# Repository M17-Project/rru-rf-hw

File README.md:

[![CC BY-NC-SA 4.0][cc-by-nc-sa-shield]][cc-by-nc-sa]

# rru-rf-hw
Remote Radio Unit RF board.

## What is it?
An FM repeater in a milled aluminum chassis. Built around a pair of [CC1200 chips](https://www.ti.com/product/CC1200) from Texas Instruments and an RF power amplifier module.
Revision A with CC1200 RF front-ends supports various FM-based modes, including M17 and AFSK.

## Quick fact sheet
RF power module - [RA60H3847M1](https://www.mitsubishielectric.com/semiconductors/hf/products/datasheet/ra60h3847m1.pdf)<br>
RF output power - 1..60W continuous, up to 80W with lower duty cycle<br>
Frequency range - 420..450MHz<br>
Frequency error - <0.5 ppm over -40 to +85°C range<br>
Supply voltage - 13.8V DC<br>
Power consumption - <150W at 60W RF out<br>
Load mismatch immunity - continuous over the whole VSWR range (built in RF isolator)<br>
Harmonic content - 2nd <-40dBc, 3rd <-55dBc (435MHz at 48.3dBm)<br>
Mode support: analog FM, M17, (A)FSK<br>
Circulator:  WH3538X-1, 400..470MHz (microstrip)<br>
Dummy load: Anaren [J100N50X4B](https://www.mouser.pl/datasheet/2/21/J100N50X4B-3364610.pdf)<br>

## Firmware
A basic, "crash-test" frmware template is available [here](https://github.com/M17-Project/rru-rf-fw).

### Flashing the MCU over UART
- Build the firmware using CubeIDE
- Copy the .bin file over to Raspberry Pi
- Run `stm32flash -v -R -i "-539&-529&539,529,:-539,-529,529" -w rru-rf-fw.bin /dev/ttyAMA0`

In case of problems, see [this](https://github.com/M17-Project/rpi-interface?tab=readme-ov-file#flashing-the-target-device-cc1200-hat) for some additional explanation.

## Chassis
Milled aluminum chassis is required. A reference design can be obtained from a [separate repository](https://github.com/M17-Project/rru-rf-chassis).

## Revision history
### Revision A
Initial revision.

### Revision B
* Switched mode voltage regulators have been replaced with linear.
* Added a buffer between the 40 MHz reference TCXO and transceiver ICs.
* Added bleeder resistors at the RF PA and 13.8V power supply.
* Slightly improved ALC circuit.
* Reduced N-connector cutouts (4.5mm down to 2mm).
* Added decoupling capacitor arrays at both RF PA's supply and VGG pins.
* DA15 connector now has MCU's BOOT0 signal available at pin 13.
* Bodge wire mod is no longer required, as both baseband trigger signals are now routed to the MCU.

### Revision C
* Added a lowpass filter after the RF PA stage
* Added a bandpass filter at the RF input
* TX and RX blocks are now clocked independently
* Pull-down resistor at TP2 (BOOT1)

## License
This work is licensed under a
[Creative Commons Attribution-NonCommercial-ShareAlike 4.0 International License][cc-by-nc-sa].

[![CC BY-NC-SA 4.0][cc-by-nc-sa-image]][cc-by-nc-sa]

[cc-by-nc-sa]: http://creativecommons.org/licenses/by-nc-sa/4.0/
[cc-by-nc-sa-image]: https://licensebuttons.net/l/by-nc-sa/4.0/88x31.png
[cc-by-nc-sa-shield]: https://img.shields.io/badge/License-CC%20BY--NC--SA%204.0-lightgrey.svg

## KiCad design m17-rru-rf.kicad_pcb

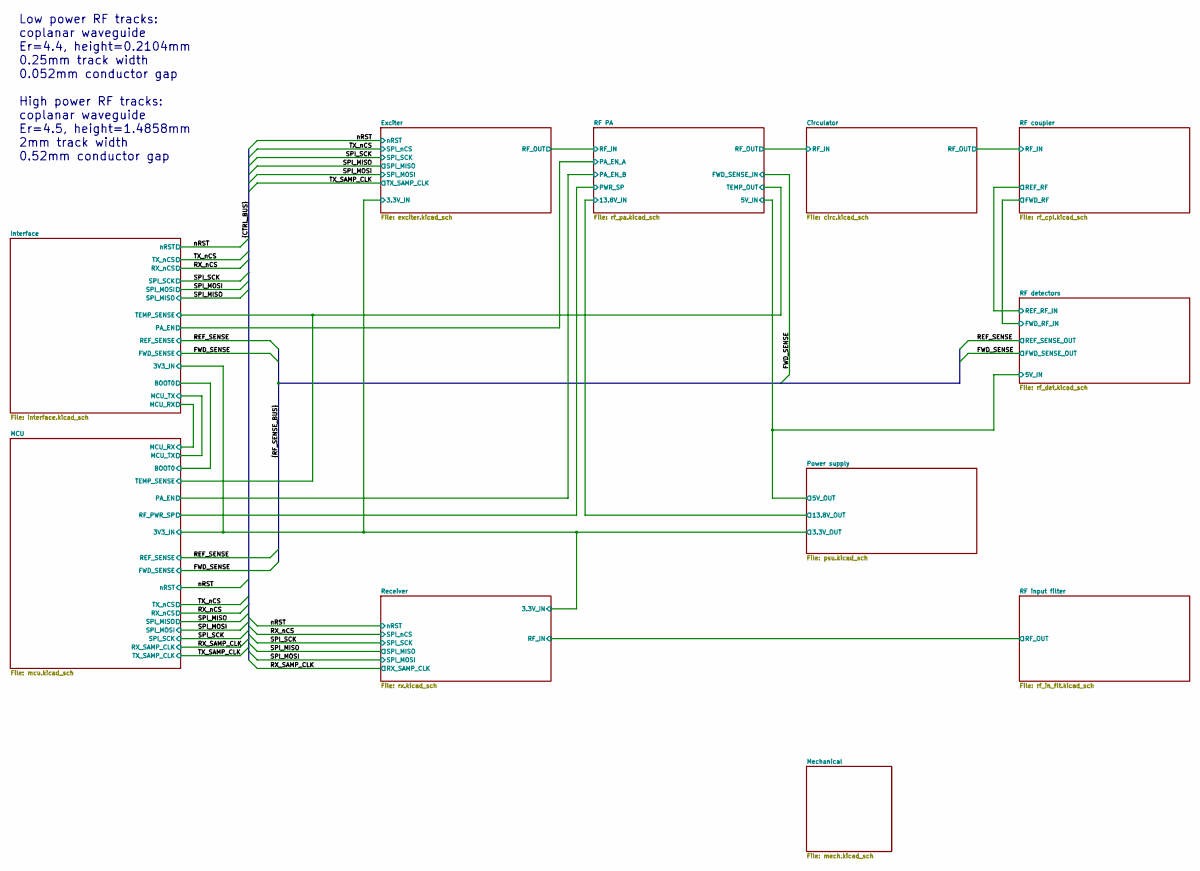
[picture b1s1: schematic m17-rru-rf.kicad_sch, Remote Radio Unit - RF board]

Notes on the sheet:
Low power RF tracks: coplanar waveguide Er=4.4, height=0.2104mm 0.25mm track width 0.052mm conductor gap High power RF tracks: coplanar waveguide Er=4.5, height=1.4858mm 2mm track width 0.52mm conductor gap

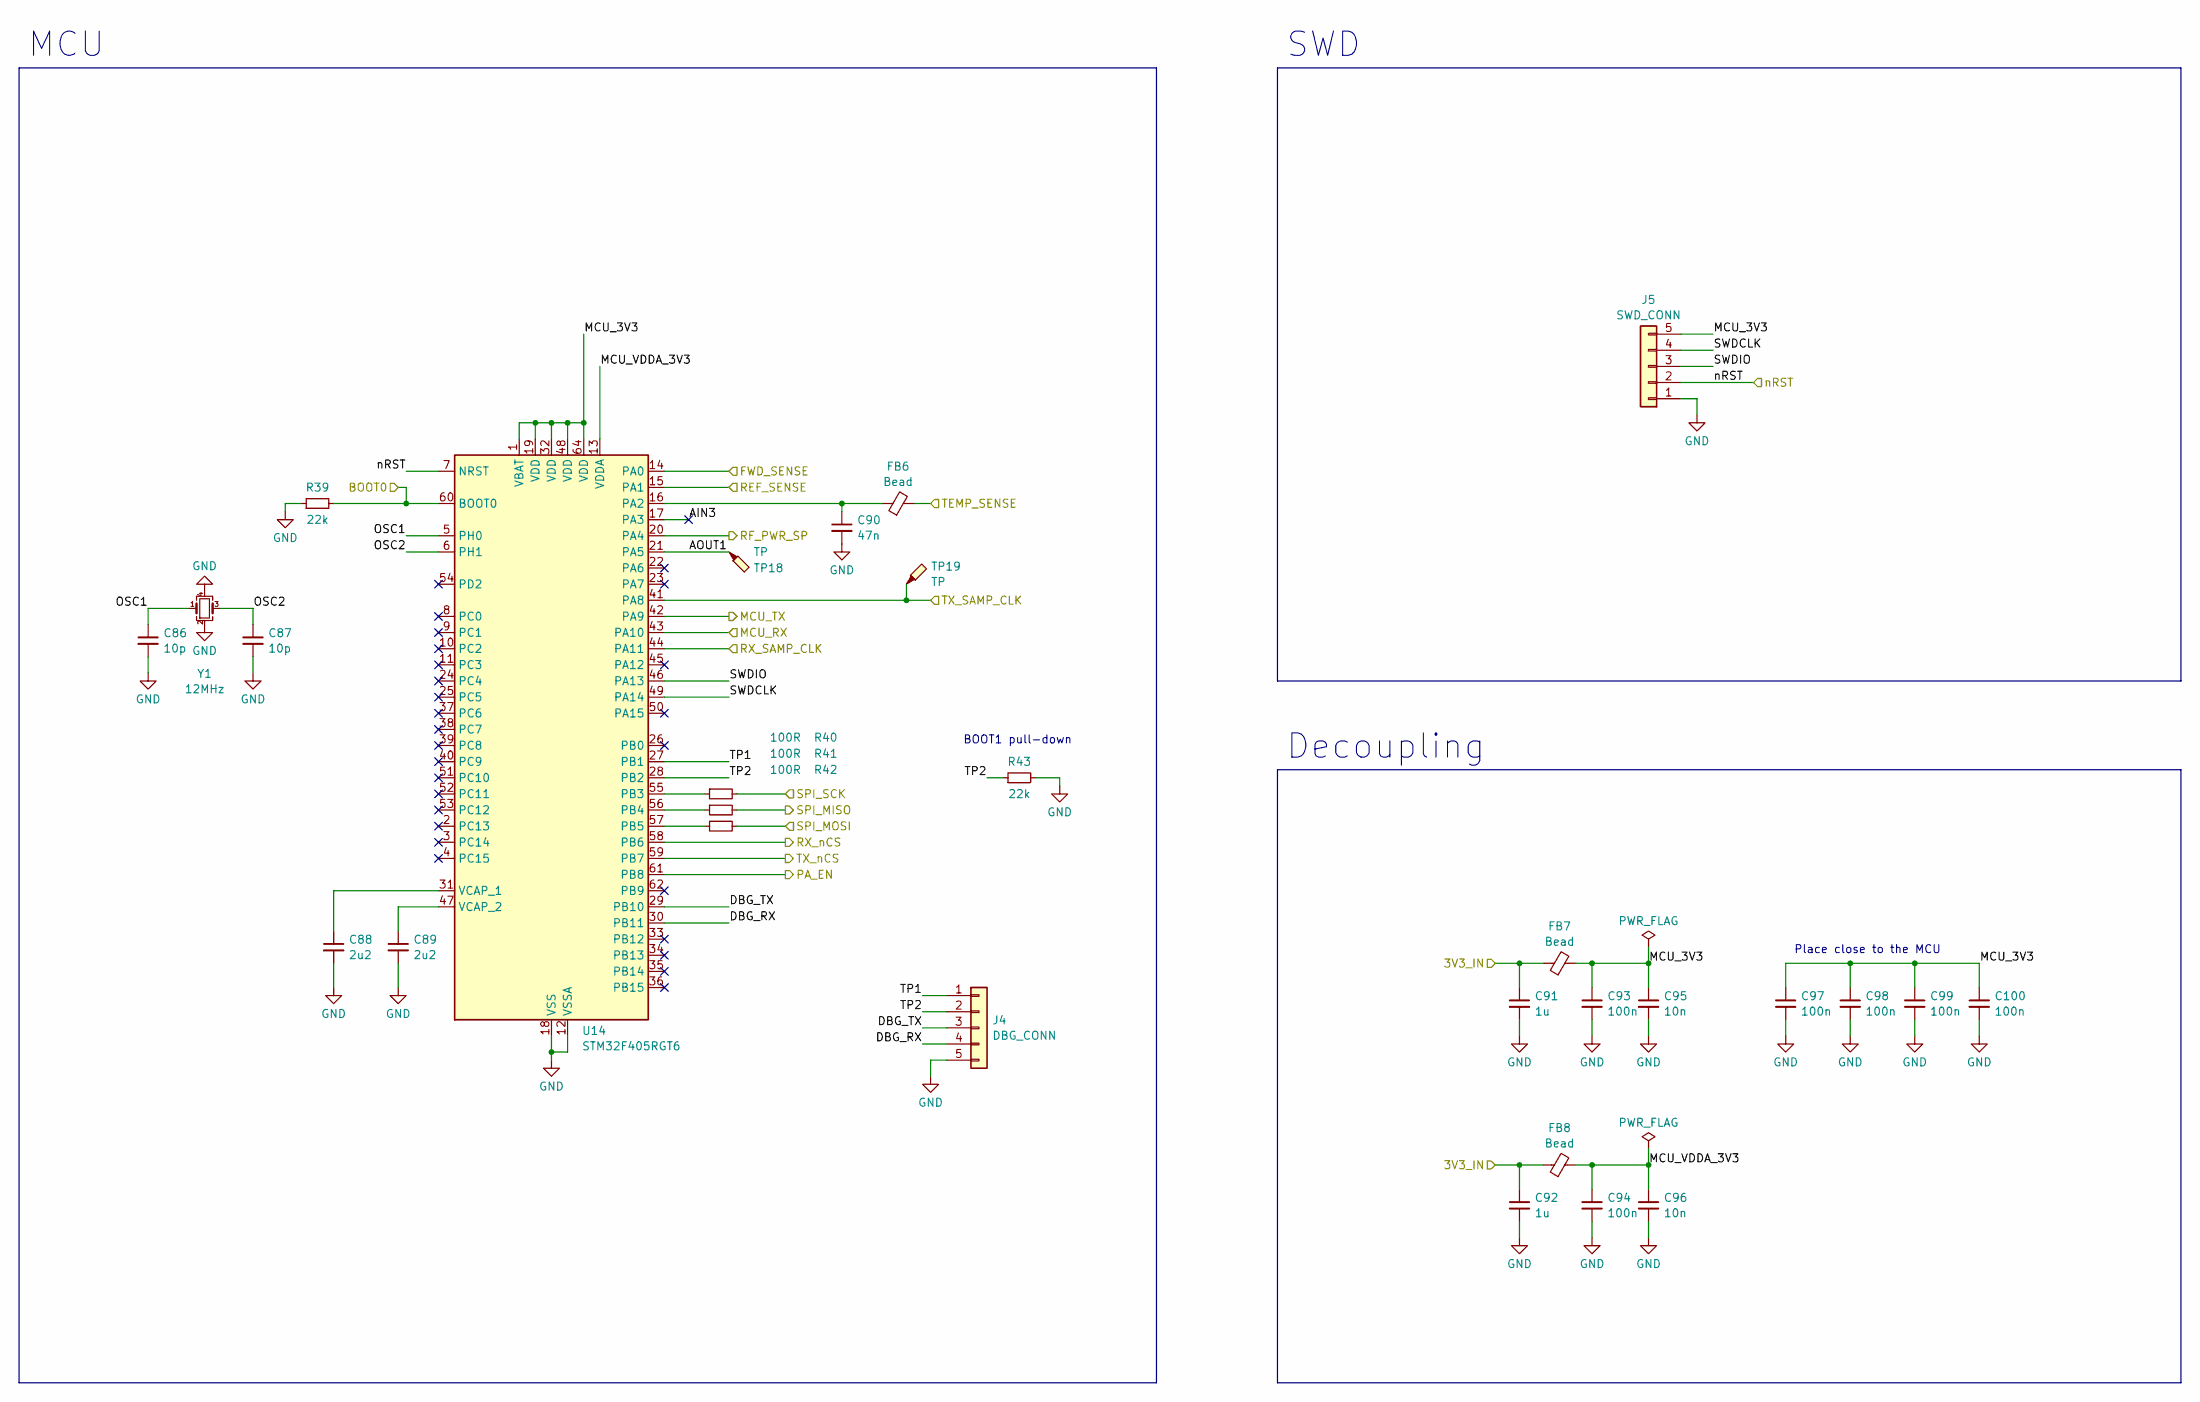
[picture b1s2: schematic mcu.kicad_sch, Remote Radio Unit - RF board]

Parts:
C86, C87: 10p; C_0603_1608Metric; MPN 06035A100JAT2A
C88, C89: 2u2; C_0603_1608Metric; MPN GRM188R61H225ME11J
C90: 47n; C_0603_1608Metric; MPN C0603C473K5RACTU
C91, C92: 1u; C_0603_1608Metric; MPN CL10B105KB8NQNC
C93, C94, C97, C98, C99, C100: 100n; C_0603_1608Metric; MPN C0603C104M5RAC7411
C95, C96: 10n; C_0603_1608Metric; MPN C0603C103K5RAC7081
FB6, FB7, FB8: Bead; L_0603_1608Metric; MPN BLM18KG601SH1D
J4: DBG_CONN; PinHeader_1x05_P2.54mm_Vertical_SMD_Pin1Left; MPN TSM-105-01-T-SV-TR
J5: SWD_CONN; PinHeader_1x05_P2.54mm_Vertical_SMD_Pin1Left; MPN TSM-105-01-T-SV-TR
R39, R43: 22k; R_0603_1608Metric; MPN CRGCQ0603J22K
R40, R41, R42: 100R; R_0603_1608Metric; MPN CRCW0603100RFKECC
TP18, TP19: TP; TestPoint_Pad_D1.5mm
U14: STM32F405RGT6; LQFP-64_10x10mm_P0.5mm; MPN STM32F405RGT6
Y1: 12MHz; Crystal_SMD_3225-4Pin_3.2x2.5mm; MPN ECS-120-12-33-AEN-TR

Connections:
/Exciter/3.3V_IN: C91.1, C92.1, FB7.1, FB8.1; also elsewhere on the board
/FWD_SENSE: U14.14 (PA0); also elsewhere on the board
/Interface/BOOT0: R39.2, U14.60 (BOOT0); also elsewhere on the board
/Interface/MCU_RX: U14.43 (PA10); also elsewhere on the board
/Interface/MCU_TX: U14.42 (PA9); also elsewhere on the board
/Interface/TEMP_SENSE: FB6.2; also elsewhere on the board
/MCU/AIN3: U14.17 (PA3)
/MCU/AOUT1: TP18.1, U14.21 (PA5)
/MCU/DBG_RX: J4.4, U14.30 (PB11)
/MCU/DBG_TX: J4.3, U14.29 (PB10)
/MCU/MCU_3V3: C93.1, C95.1, C97.1, C98.1, C99.1, C100.1, FB7.2, J5.5, U14.1 (VBAT), U14.19 (VDD), U14.32 (VDD), U14.48 (VDD), U14.64 (VDD)
/MCU/MCU_VDDA_3V3: C94.1, C96.1, FB8.2, U14.13 (VDDA)
/MCU/OSC1: C86.1, U14.5 (PH0), Y1.1
/MCU/OSC2: C87.1, U14.6 (PH1), Y1.3
/MCU/PA_EN: U14.61 (PB8); also elsewhere on the board
/MCU/RF_PWR_SP: U14.20 (PA4); also elsewhere on the board
/MCU/SWDCLK: J5.4, U14.49 (PA14)
/MCU/SWDIO: J5.3, U14.46 (PA13)
/MCU/TP1: J4.1, U14.27 (PB1)
/MCU/TP2: J4.2, R43.1, U14.28 (PB2)
/REF_SENSE: U14.15 (PA1); also elsewhere on the board
/RX_SAMP_CLK: U14.44 (PA11); also elsewhere on the board
/RX_nCS: U14.58 (PB6); also elsewhere on the board
/SPI_MISO: R41.2; also elsewhere on the board
/SPI_MOSI: R42.2; also elsewhere on the board
/SPI_SCK: R40.2; also elsewhere on the board
/TX_SAMP_CLK: TP19.1, U14.41 (PA8); also elsewhere on the board
/TX_nCS: U14.59 (PB7); also elsewhere on the board
/nRST: J5.2, U14.7 (NRST); also elsewhere on the board
GND: C86.2, C87.2, C88.2, C89.2, C90.2, C91.2, C92.2, C93.2, C94.2, C95.2, C96.2, C97.2, C98.2, C99.2, C100.2, J4.5, J5.1, R39.1, R43.2, U14.12 (VSSA), U14.18 (VSS), U14.63 (VSS), Y1.2, Y1.4; also elsewhere on the board
unnamed: C90.1, FB6.1, U14.16 (PA2)
unnamed: R40.1, U14.55 (PB3)
unnamed: R41.1, U14.56 (PB4)
unnamed: R42.1, U14.57 (PB5)
unnamed: C88.1, U14.31 (VCAP_1)
unnamed: C89.1, U14.47 (VCAP_2)

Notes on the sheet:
MCU
Place close to the MCU
BOOT1 pull-down
SWD
Decoupling

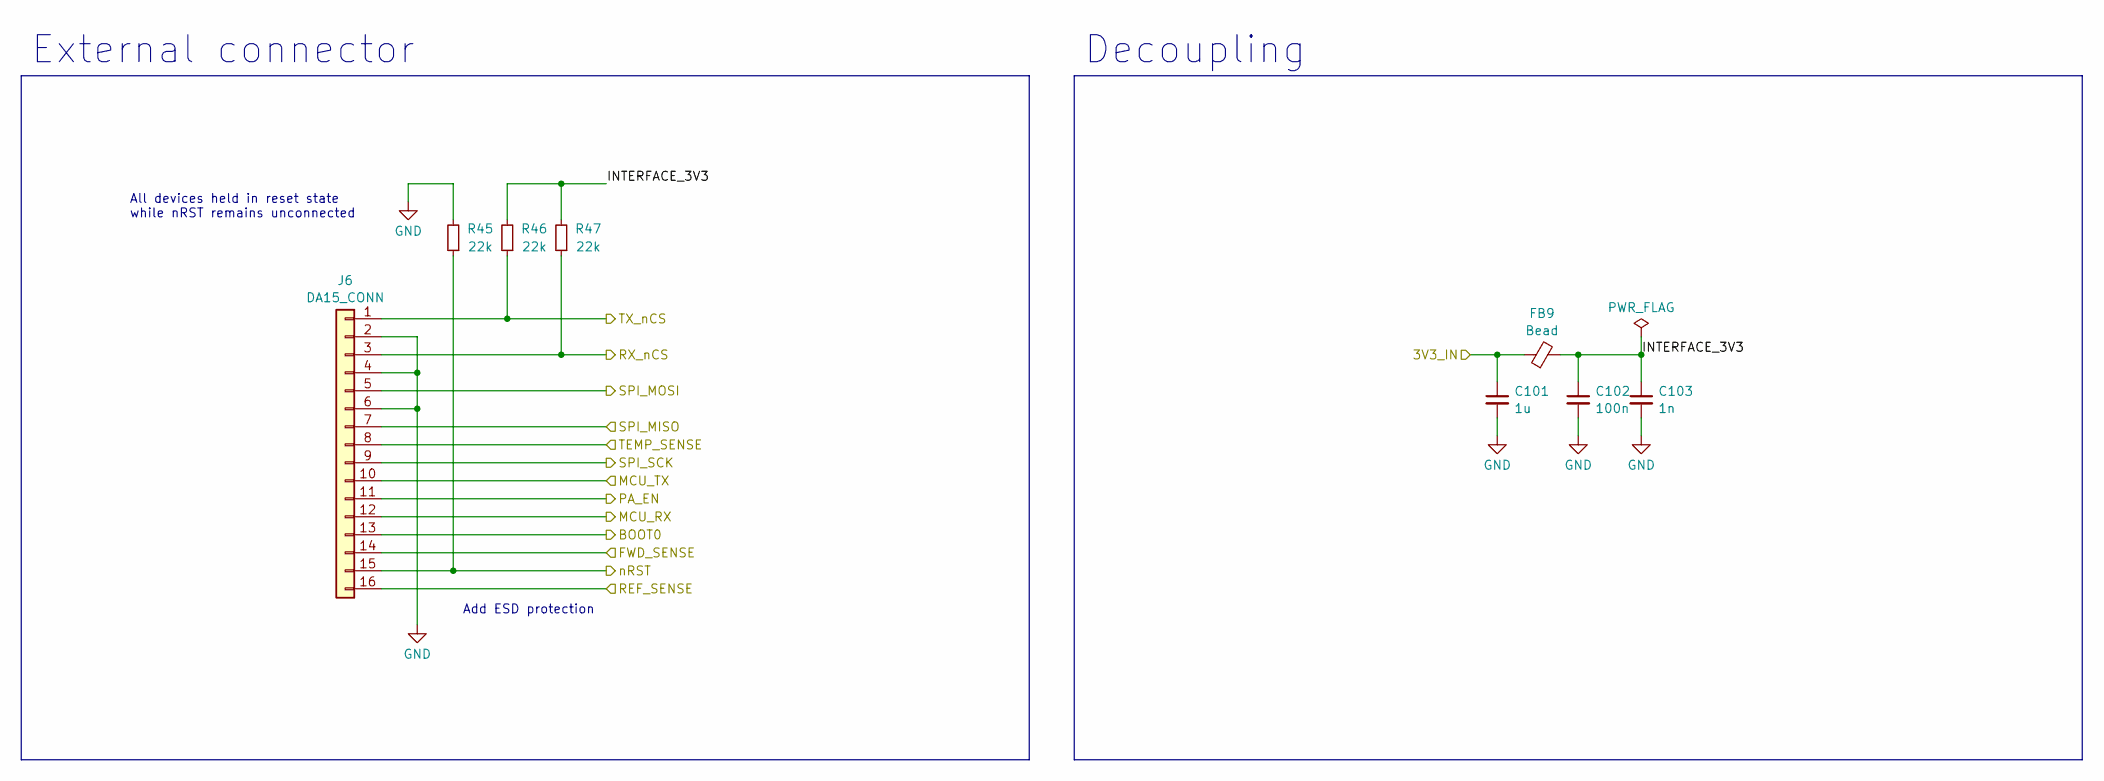
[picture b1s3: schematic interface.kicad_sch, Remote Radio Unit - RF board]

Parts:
C101: 1u; C_0603_1608Metric; MPN CL10B105KB8NQNC
C102: 100n; C_0603_1608Metric; MPN C0603C104M5RAC7411
C103: 1n; C_0603_1608Metric; MPN C0603C102J5GAC7411
FB9: Bead; L_0603_1608Metric; MPN BLM18KG601SH1D
J6: DA15_CONN; PinHeader_2x08_P2.54mm_Vertical_SMD; MPN TSM-108-01-L-DV-P-TR
R45, R46, R47: 22k; R_0603_1608Metric; MPN CRGCQ0603J22K

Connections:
/Exciter/3.3V_IN: C101.1, FB9.1; also elsewhere on the board
/FWD_SENSE: J6.14; also elsewhere on the board
/Interface/BOOT0: J6.13; also elsewhere on the board
/Interface/INTERFACE_3V3: C102.1, C103.1, FB9.2, R46.2, R47.2
/Interface/MCU_RX: J6.12; also elsewhere on the board
/Interface/MCU_TX: J6.10; also elsewhere on the board
/Interface/PA_EN: J6.11; also elsewhere on the board
/Interface/TEMP_SENSE: J6.8; also elsewhere on the board
/REF_SENSE: J6.16; also elsewhere on the board
/RX_nCS: J6.3, R47.1; also elsewhere on the board
/SPI_MISO: J6.7; also elsewhere on the board
/SPI_MOSI: J6.5; also elsewhere on the board
/SPI_SCK: J6.9; also elsewhere on the board
/TX_nCS: J6.1, R46.1; also elsewhere on the board
/nRST: J6.15, R45.1; also elsewhere on the board
GND: C101.2, C102.2, C103.2, J6.2, J6.4, J6.6, R45.2; also elsewhere on the board

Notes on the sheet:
Decoupling
External connector
All devices held in reset state while nRST remains unconnected
Add ESD protection

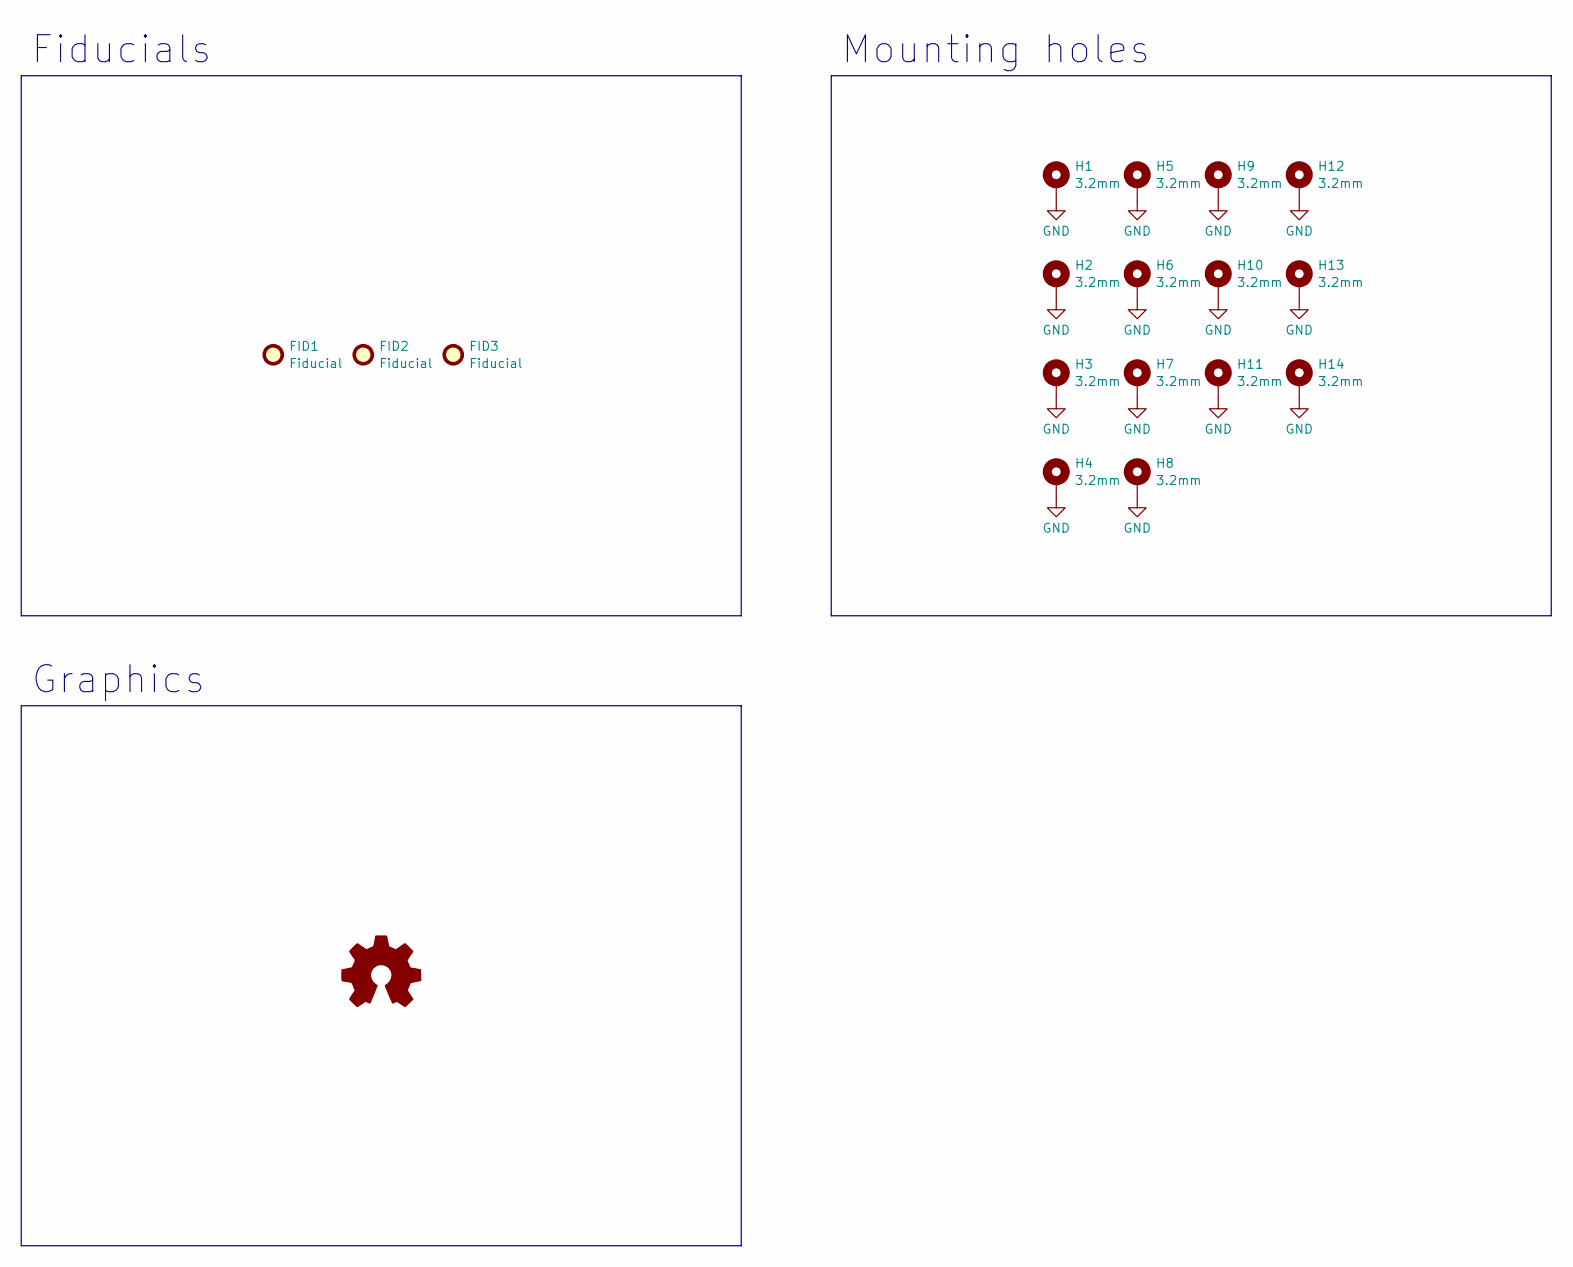
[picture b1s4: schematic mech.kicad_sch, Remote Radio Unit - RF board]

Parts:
FID1, FID2, FID3: Fiducial; Fiducial_0.75mm_Mask1.5mm
H1, H2, H3, H4, H5, H6, H7, H8, H9, H10, H11, H12, H13, H14: 3.2mm; MountingHole_3.2mm_M3_Pad_Via

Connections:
GND: H1.1, H2.1, H3.1, H4.1, H5.1, H6.1, H7.1, H8.1, H9.1, H10.1, H11.1, H12.1, H13.1, H14.1; also elsewhere on the board

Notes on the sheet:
Mounting holes
Graphics
Fiducials

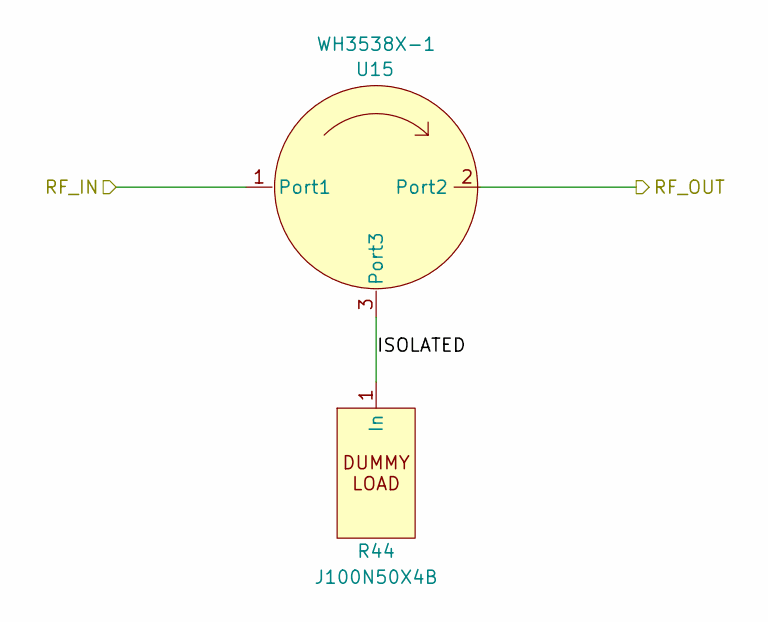
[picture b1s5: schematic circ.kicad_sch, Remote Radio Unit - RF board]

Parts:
R44: J100N50X4B; HALF_FLANGE_DUMMY_LOAD; MPN J100N50X4B
U15: WH3538X-1; CIRC_H08; MPN WH3538X-1

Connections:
/Circulator/ISOLATED: R44.1 (In), U15.3 (Port3)
/Circulator/RF_IN: U15.1 (Port1); also elsewhere on the board
/Circulator/RF_OUT: U15.2 (Port2); also elsewhere on the board

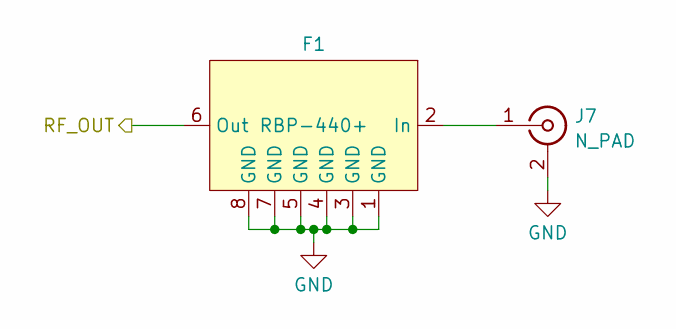
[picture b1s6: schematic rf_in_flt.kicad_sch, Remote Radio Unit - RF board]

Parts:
F1: RBP-440+; RBP_CASE; MPN RBP-440+
J7: N_PAD; SMA_Samtec_SMA-J-P-X-ST-EM1_EdgeMount

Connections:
/RF input filter/RF_OUT: F1.6 (Out); also elsewhere on the board
GND: F1.1 (GND), F1.3 (GND), F1.4 (GND), F1.5 (GND), F1.7 (GND), F1.8 (GND), J7.2 (Ext); also elsewhere on the board
unnamed: F1.2 (In), J7.1 (In)

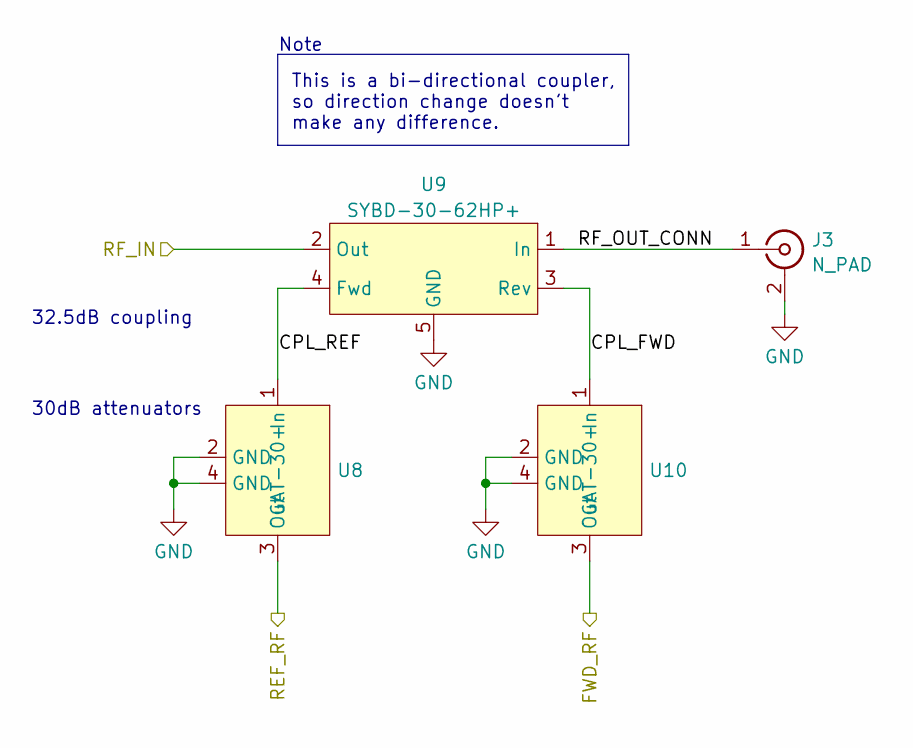
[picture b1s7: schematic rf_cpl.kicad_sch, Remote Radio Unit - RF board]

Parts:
J3: N_PAD; SMA_Samtec_SMA-J-P-X-ST-EM1_EdgeMount
U8, U10: GAT-30+; GAT-30_LAND; MPN 139-GAT-30+
U9: SYBD-30-62HP+; SYBD-30_LAND; MPN SYBD-30-62HP+

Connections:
/Circulator/RF_OUT: U9.2 (Out); also elsewhere on the board
/RF coupler/CPL_FWD: U9.3 (Rev), U10.1 (In)
/RF coupler/CPL_REF: U8.1 (In), U9.4 (Fwd)
/RF coupler/FWD_RF: U10.3 (Out); also elsewhere on the board
/RF coupler/REF_RF: U8.3 (Out); also elsewhere on the board
/RF coupler/RF_OUT_CONN: J3.1 (In), U9.1 (In)
GND: J3.2 (Ext), U8.2 (GND), U8.4 (GND), U9.5 (GND), U10.2 (GND), U10.4 (GND); also elsewhere on the board

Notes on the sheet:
Note
30dB attenuators
This is a bi-directional coupler, so direction change doesn't make any difference.
32.5dB coupling

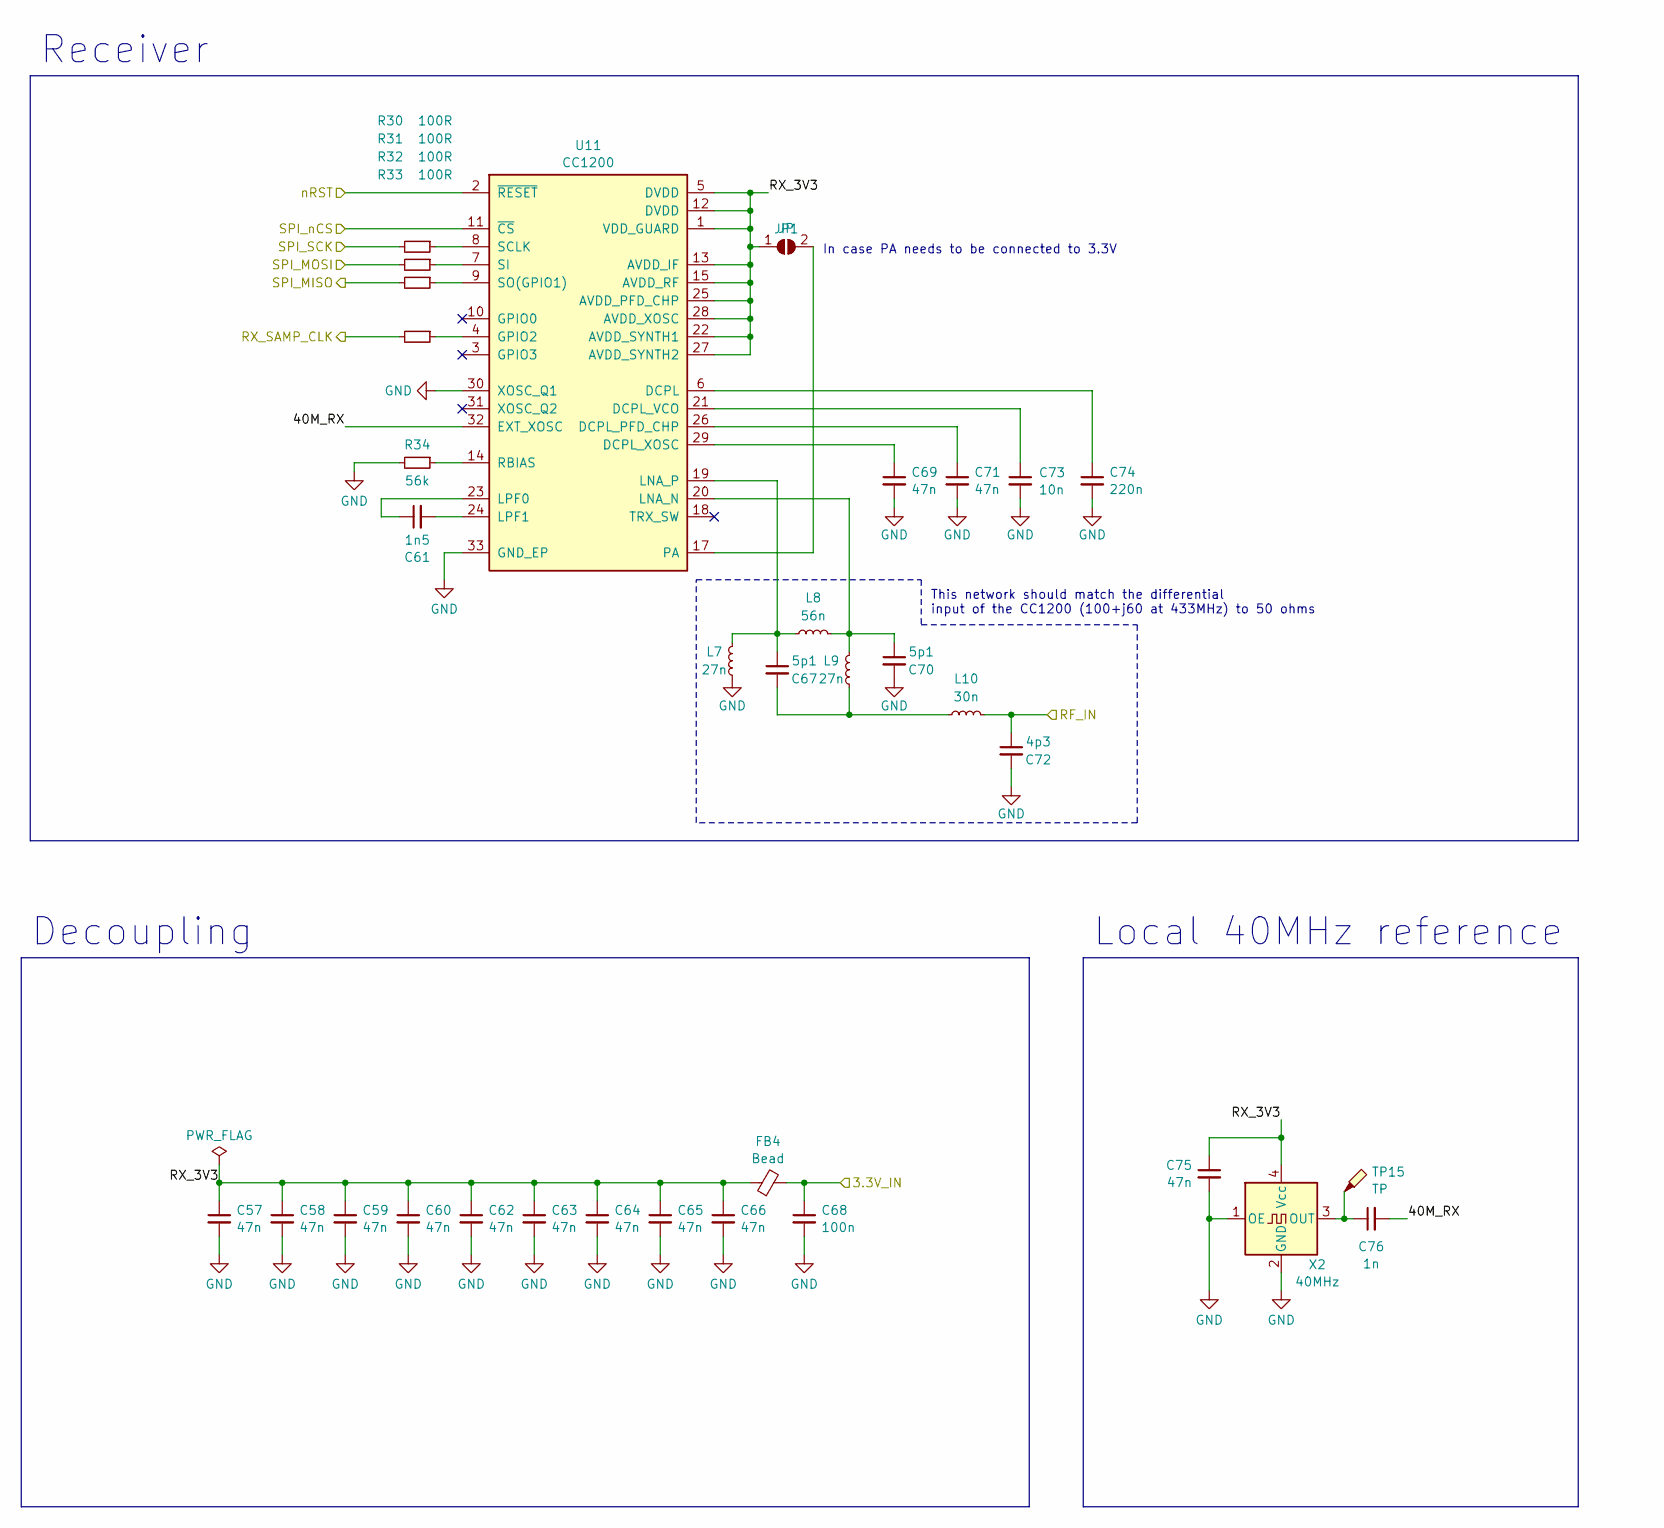
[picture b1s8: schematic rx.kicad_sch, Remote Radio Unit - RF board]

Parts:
C57, C58, C59, C60, C62, C63, C64, C65, C66, C69, C71, C75: 47n; C_0603_1608Metric; MPN C0603C473K5RACTU
C61: 1n5; C_0603_1608Metric; MPN GRM1885C1H152JA01D
C67, C70: 5p1; C_0603_1608Metric; MPN CC0603CRNPO9BN5R1
C68: 100n; C_0603_1608Metric; MPN C0603C104M5RAC7411
C72: 4p3; C_0603_1608Metric; MPN CBR06C439C5GAC
C73: 10n; C_0603_1608Metric; MPN C0603C103K5RAC7081
C74: 220n; C_0603_1608Metric; MPN C0603C224K4RACTU
C76: 1n; C_0603_1608Metric; MPN C0603C102J5GAC7411
FB4: Bead; L_0603_1608Metric; MPN BLM18KG601SH1D
JP1: JP; SolderJumper-2_P1.3mm_Open_TrianglePad1.0x1.5mm
L7, L9: 27n; L_0603_1608Metric; MPN LQW18AN27NG00D
L8: 56n; L_0603_1608Metric; MPN 81-LQW18AN56NG00D
L10: 30n; L_0603_1608Metric; MPN LQW18AN30NG00D
R30, R31, R32, R33: 100R; R_0603_1608Metric; MPN CRCW0603100RFKECC
R34: 56k; R_0603_1608Metric; MPN CRGCQ0603F56K
TP15: TP; TestPoint_Pad_D1.5mm
U11: CC1200; QFN-32-1EP_5x5mm_P0.5mm_EP3.45x3.45mm; MPN CC1200RHBR
X2: 40MHz; Oscillator_SMD_SeikoEpson_SG210-4Pin_2.5x2.0mm; MPN FT2MNTUM-40.0-T1

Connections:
/Exciter/3.3V_IN: C68.1, FB4.2; also elsewhere on the board
/RF input filter/RF_OUT: C72.1, L10.1; also elsewhere on the board
/RX_SAMP_CLK: R33.2; also elsewhere on the board
/RX_nCS: U11.11 (~CS); also elsewhere on the board
/Receiver/40M_RX: C76.2, U11.32 (EXT_XOSC)
/Receiver/RX_3V3: C57.1, C58.1, C59.1, C60.1, C62.1, C63.1, C64.1, C65.1, C66.1, C75.1, FB4.1, JP1.1 (A), U11.1 (VDD_GUARD), U11.5 (DVDD), U11.12 (DVDD), U11.13 (AVDD_IF), U11.15 (AVDD_RF), U11.22 (AVDD_SYNTH1), U11.25 (AVDD_PFD_CHP), U11.27 (AVDD_SYNTH2), U11.28 (AVDD_XOSC), X2.4 (Vcc)
/SPI_MISO: R32.2; also elsewhere on the board
/SPI_MOSI: R31.2; also elsewhere on the board
/SPI_SCK: R30.2; also elsewhere on the board
/nRST: U11.2 (~RESET); also elsewhere on the board
GND: C57.2, C58.2, C59.2, C60.2, C62.2, C63.2, C64.2, C65.2, C66.2, C68.2, C69.2, C70.2, C71.2, C72.2, C73.2, C74.2, C75.2, L7.2, R34.2, U11.30 (XOSC_Q1), U11.33 (GND_EP), X2.1 (OE), X2.2 (GND); also elsewhere on the board
unnamed: C67.2, L9.2, L10.2
unnamed: JP1.2 (B), U11.17 (PA)
unnamed: C74.1, U11.6 (DCPL)
unnamed: C71.1, U11.26 (DCPL_PFD_CHP)
unnamed: C73.1, U11.21 (DCPL_VCO)
unnamed: C69.1, U11.29 (DCPL_XOSC)
unnamed: R33.1, U11.4 (GPIO2)
unnamed: C70.1, L8.1, L9.1, U11.20 (LNA_N)
unnamed: C67.1, L7.1, L8.2, U11.19 (LNA_P)
unnamed: C61.1, U11.23 (LPF0)
unnamed: C61.2, U11.24 (LPF1)
unnamed: R34.1, U11.14 (RBIAS)
unnamed: R30.1, U11.8 (SCLK)
unnamed: R31.1, U11.7 (SI)
unnamed: R32.1, U11.9 (SO(GPIO1))
unnamed: C76.1, TP15.1, X2.3 (OUT)

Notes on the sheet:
Local 40MHz reference
Decoupling
Receiver
This network should match the differential input of the CC1200 (100+j60 at 433MHz) to 50 ohms
In case PA needs to be connected to 3.3V

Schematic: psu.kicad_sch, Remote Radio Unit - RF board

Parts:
C26, C27, C30: 100u/50V; CP_Elec_8x10.5; MPN 50SEV100M8X10.5
C28, C29: 100n; C_0603_1608Metric; MPN C0603C104M5RAC7411
C31, C32: 22u/6.3V; C_0603_1608Metric; MPN GRM188R60J226MEA0J
D6, D7: B160-13-F; D_SMA; MPN B160-13-F
J2: 13.8V; TestPoint_Pad_D3.0mm
R23: 100k; R_0603_1608Metric; MPN CRCW0603100KFKEAC
TP11, TP12, TP13: TP; TestPoint_Pad_D1.5mm
U5: KF33BDT; TO-252-2; MPN 511-KF33BDT-TR
U6: KF50BDT; TO-252-2; MPN 511-KF50BDT-TR

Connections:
/Exciter/3.3V_IN: C31.2, D6.2 (A), TP12.1, U5.3 (VO); also elsewhere on the board
/Power supply/5V_OUT: C32.2, D7.2 (A), TP13.1, U6.3 (VO); also elsewhere on the board
/Power supply/13.8V_OUT: C26.1, C27.1, C28.1, C29.1, C30.1, D6.1 (K), D7.1 (K), J2.1, R23.1, TP11.1, U5.1 (VI), U6.1 (VI); also elsewhere on the board
GND: C26.2, C27.2, C28.2, C29.2, C30.2, C31.1, C32.1, R23.2, U5.2 (GND), U6.2 (GND); also elsewhere on the board

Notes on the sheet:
Voltage reg.

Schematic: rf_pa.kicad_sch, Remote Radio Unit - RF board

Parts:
C1, C2, C3, C7, C9, C13, C14: 100n; C_0603_1608Metric; MPN C0603C104M5RAC7411
C4: 3n9; C_0603_1608Metric; MPN GCM1885C1H392JA16J; not fitted
C5: 3n9; C_0603_1608Metric; MPN GCM1885C1H392JA16J
C6, C15: 1u; C_0603_1608Metric; MPN CL10B105KB8NQNC
C8, C11, C22: 1n; C_0603_1608Metric; MPN C0603C102J5GAC7411
C10, C19: 10n; C_0603_1608Metric; MPN C0603C103K5RAC7081
C12, C23: 100p; C_0603_1608Metric; MPN VJ0603A101JXAPW1BC
C16: 100u/50V; CP_Elec_8x10.5; MPN 50SEV100M8X10.5
C17, C18, C20: 1p5; C_1206_3216Metric_Pad1.33x1.80mm_HandSolder; MPN 12067A1R5CAT2A
C21: 8p2; C_1206_3216Metric_Pad1.33x1.80mm_HandSolder; MPN 12067A8R2BAT2A
C24: DNP; C_1206_3216Metric_Pad1.33x1.80mm_HandSolder; not fitted
C25: 2p7; C_1206_3216Metric_Pad1.33x1.80mm_HandSolder; MPN 12062A2R7CAT2A
D1, D2: B160-13-F; D_SMA; MPN B160-13-F
D3: MM3Z4V7S; D_SOD-323; MPN MM3Z4V7ST1G
D4, D5: SS1P4L; DO-220AA-SMP; MPN SS1P4LHM3/84A
FB1, FB2: Bead; L_0603_1608Metric; MPN BLM18KG601SH1D
J1: LMT87LPM; PinHeader_1x03_P2.54mm_Vertical_SMD_Pin1Left; MPN TSM-103-01-T-SV-TR
L1: 24nH; aircoil_L; not fitted
L2: 24nH; aircoil_R; not fitted
Q1, Q2: BSS138; SOT-23; MPN BSS138P,215
Q3: NP100P04PDG; TO-263-2; MPN NP100P04PDG-E1-AY
R1: 7k5; R_0603_1608Metric; MPN RK73H1JTTD7501F
R2: 22k; R_0603_1608Metric; MPN CRGCQ0603J22K
R3: 4k7; R_0603_1608Metric; MPN RK73B1JRTTD472J
R4, R11, R19, R22: 100k; R_0603_1608Metric; MPN CRCW0603100KFKEAC
R5, R9, R10, R12, R18, R20: 10k; R_0603_1608Metric; MPN RT0603FRE0710KL
R6: 240R; R_0603_1608Metric; MPN WR06X2400FTL
R7: 1k; R_0603_1608Metric; MPN RC0603FR-071KL
R8, R13, R16, R17: 100R; R_0603_1608Metric; MPN CRCW0603100RFKECC
R14, R21: 12k; R_0603_1608Metric; MPN CRCW060312K0FKEAC
R15: 2k2; R_0603_1608Metric; MPN CRCW06032K20FKEAC
TP1, TP2, TP3, TP4, TP5, TP6, TP7, TP8, TP9, TP10: TP; TestPoint_Pad_D1.5mm
U1: LM317_SOT-223; SOT-223-3_TabPin2; MPN LM317MDCYRG3
U2: LT1013DIDR; SOIC127P600X175-8N; Mouser Part Number 595-LT1013DIDR
U3: TL431; SOT-23; MPN TL431LIBIDBZR
U4: RA60H3847H1; H2M

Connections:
/Circulator/RF_IN: C24.2, C25.1, L2.2; also elsewhere on the board
/Exciter/RF_OUT: U4.1 (In); also elsewhere on the board
/FWD_SENSE: R5.1, TP2.1; also elsewhere on the board
/Interface/PA_EN: R16.1; also elsewhere on the board
/Interface/TEMP_SENSE: J1.2; also elsewhere on the board
/MCU/PA_EN: R17.1; also elsewhere on the board
/MCU/RF_PWR_SP: R1.1; also elsewhere on the board
/Power supply/5V_OUT: C15.1, FB2.1; also elsewhere on the board
/Power supply/13.8V_OUT: C1.1, D1.1 (K), D5.1 (K), Q3.3 (S), R21.2, U1.3 (VI); also elsewhere on the board
/RF PA/PA_OUT: C17.2, C18.1, L1.1, U4.4 (Out)
/RF PA/PA_OUT_2: C20.2, C21.1, L1.2, L2.1
/RF PA/RF_PA_1V1: C9.1, R12.2, R14.2, TP6.1, U2.1 (1IN+)
/RF PA/RF_PA_7V: C7.1, C8.1, FB1.2, R15.2, TP5.1, U2.6 (VCC+)
/RF PA/RF_PA_VDD: C16.1, C19.1, C22.2, C23.1, D4.1 (K), D5.2 (A), Q3.2 (D), R22.1, U4.3 (VDD)
/RF PA/RF_PA_VGG: C10.1, C11.2, C12.1, D3.1 (K), R13.1, U4.2 (VGG)
/RF PA/VGG_RAW: C5.1, R11.2, R13.2, TP3.1, U2.5 (2OUT)
GND: C1.2, C2.2, C3.2, C6.2, C7.2, C8.2, C9.2, C10.2, C11.1, C12.2, C13.1, C14.2, C15.2, C16.2, C17.1, C18.2, C19.2, C20.1, C21.2, C22.1, C23.2, C24.1, C25.2, D3.2 (A), D4.2 (A), J1.3, Q2.2 (S), R2.1, R4.1, R8.1, R12.1, R20.1, R22.2, U2.2 (VCC-), U3.3 (A); also elsewhere on the board
unnamed: C6.1, D1.2 (A), D2.1 (K), FB1.1, R6.2, U1.2 (VO)
unnamed: C3.1, D2.2 (A), R6.1, R7.2, U1.1 (ADJ)
unnamed: C14.1, FB2.2, J1.1
unnamed: Q1.3 (D), Q3.1 (G), R21.1, TP10.1
unnamed: Q1.1 (G), R16.2, R18.2, TP8.1
unnamed: Q1.2 (S), Q2.3 (D), R18.1, R19.2
unnamed: Q2.1 (G), R17.2, R19.1, R20.2, TP9.1
unnamed: R1.2, R2.2, R3.1, TP1.1
unnamed: R7.1, R8.2
unnamed: C4.2, R5.2, R9.2, U2.8 (1IN-)
unnamed: C4.1, R9.1, R10.2, TP4.1, U2.7 (1OUT)
unnamed: C2.1, R3.2, R4.2, U2.3 (2IN+)
unnamed: C5.2, R10.1, R11.1, U2.4 (2IN-)
unnamed: C13.2, R14.1, R15.1, TP7.1, U3.1 (K), U3.2 (REF)

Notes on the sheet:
Voltage reg.
RF PA
Aircoils to be populated manually
Aircoils: 0.8mm silver plated copper wire 3 turns 3.2mm inner dia ~4mm length Resulting inductance should be around 24nH
Supply switching
ALC

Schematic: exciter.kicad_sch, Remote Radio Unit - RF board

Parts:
C33, C34, C35, C36, C37, C39, C40, C41, C42, C44, C45, C50: 47n; C_0603_1608Metric; MPN C0603C473K5RACTU
C38: 1n5; C_0603_1608Metric; MPN GRM1885C1H152JA01D
C43: 100n; C_0603_1608Metric; MPN C0603C104M5RAC7411
C46, C52: 10n; C_0603_1608Metric; MPN C0603C103K5RAC7081
C47: 220n; C_0603_1608Metric; MPN C0603C224K4RACTU
C48: 39p; C_0603_1608Metric; MPN CL10C390JB81PNC
C49: 56p; C_0603_1608Metric; MPN 0603N560F500CT
C51: 2p2; C_0603_1608Metric; MPN CC0603BRNPO9BN2R2
C53: 5p1; C_0603_1608Metric; MPN CC0603CRNPO9BN5R1
C54: 100p; C_0603_1608Metric; MPN VJ0603A101JXAPW1BC
C55: 6p2; C_0603_1608Metric; MPN GRM1885C1H6R2BA01D
C56: 1n; C_0603_1608Metric; MPN C0603C102J5GAC7411
FB3: Bead; L_0603_1608Metric; MPN BLM18KG601SH1D
L3: 56n; L_0603_1608Metric; MPN 81-LQW18AN56NG00D
L4: 15n; L_0603_1608Metric; MPN LQW18AS15NG00D
L5: 43n; L_0603_1608Metric; MPN LQW18AN43NJ00D
L6: 22n; L_0603_1608Metric; MPN LQW18AN22NG00D
R24, R25, R26, R27: 100R; R_0603_1608Metric; MPN CRCW0603100RFKECC
R28: 56k; R_0603_1608Metric; MPN CRGCQ0603F56K
R29: 18R; R_0603_1608Metric; MPN RC0603FR-0718RL
TP14: TP; TestPoint_Pad_D1.5mm
U7: CC1200; QFN-32-1EP_5x5mm_P0.5mm_EP3.45x3.45mm; MPN CC1200RHBR
X1: 40MHz; Oscillator_SMD_SeikoEpson_SG210-4Pin_2.5x2.0mm; MPN FT2MNTUM-40.0-T1

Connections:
/Exciter/3.3V_IN: C43.1, FB3.2; also elsewhere on the board
/Exciter/40M_TX: C56.2, U7.32 (EXT_XOSC)
/Exciter/EXCITER_3V3: C33.1, C34.1, C35.1, C36.1, C37.1, C39.1, C40.1, C41.1, C42.1, C49.1, C50.1, C52.1, C54.1, FB3.1, R29.2, U7.1 (VDD_GUARD), U7.5 (DVDD), U7.12 (DVDD), U7.13 (AVDD_IF), U7.15 (AVDD_RF), U7.22 (AVDD_SYNTH1), U7.25 (AVDD_PFD_CHP), U7.27 (AVDD_SYNTH2), U7.28 (AVDD_XOSC), X1.4 (Vcc)
/Exciter/RF_OUT: L6.1; also elsewhere on the board
/SPI_MISO: R26.2; also elsewhere on the board
/SPI_MOSI: R25.2; also elsewhere on the board
/SPI_SCK: R24.2; also elsewhere on the board
/TX_SAMP_CLK: R27.2; also elsewhere on the board
/TX_nCS: U7.11 (~CS); also elsewhere on the board
/nRST: U7.2 (~RESET); also elsewhere on the board
GND: C33.2, C34.2, C35.2, C36.2, C37.2, C39.2, C40.2, C41.2, C42.2, C43.2, C44.2, C45.2, C46.2, C47.2, C50.2, C52.2, C53.2, C54.2, C55.2, R28.2, U7.19 (LNA_P), U7.20 (LNA_N), U7.30 (XOSC_Q1), U7.33 (GND_EP), X1.1 (OE), X1.2 (GND); also elsewhere on the board
unnamed: C48.1, C51.2, L4.2
unnamed: C49.2, L3.1, R29.1
unnamed: C51.1, C53.1, L4.1, L5.2
unnamed: C55.1, L5.1, L6.2
unnamed: C47.1, U7.6 (DCPL)
unnamed: C45.1, U7.26 (DCPL_PFD_CHP)
unnamed: C46.1, U7.21 (DCPL_VCO)
unnamed: C44.1, U7.29 (DCPL_XOSC)
unnamed: R27.1, U7.4 (GPIO2)
unnamed: C38.1, U7.23 (LPF0)
unnamed: C38.2, U7.24 (LPF1)
unnamed: C48.2, L3.2, U7.17 (PA)
unnamed: R28.1, U7.14 (RBIAS)
unnamed: R24.1, U7.8 (SCLK)
unnamed: R25.1, U7.7 (SI)
unnamed: R26.1, U7.9 (SO(GPIO1))
unnamed: C56.1, TP14.1, X1.3 (OUT)

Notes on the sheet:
Local 40MHz reference
Decoupling
Exciter
